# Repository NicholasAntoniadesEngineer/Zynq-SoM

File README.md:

# Zynq-SoM

A Zynq-7000 system-on-module + carrier board, with `schgen` — a netlist-first
KiCad schematic **and PCB** generator using C++ netlist definitions
to produce checked schematics and placed boards with component models and
multi-angle renders. Routing is deferred; these are not fabrication-ready boards.

The current published placement review is a **162×151 mm carrier** and
**98×98 mm devkit**. See the [release generation recipe and limitations](docs/RELEASE-2026-10-16.md)
to reproduce the committed images; the default commands below do not select
the carrier's qualified compact-placement recipe.

## Native build and test entry point

The C++ migration's Python-free build, dependency bootstrap and complete native
CTest entry point are documented in [`native/ci/README.md`](native/ci/README.md).
Use that path for native production builds. The transitional Python extension
and its build script are retired. Native `schgen check --tests-dir BUILD` runs
the full board, mutation/determinism selftest and complete CTest inventory.
All 393 inventoried tracked Python sources and tests are retired, along with
their dependency and lint configuration. Clean-tree acceptance is still in
progress; the commands below use the native executable.
All verification remains local, as required by the repository's no-CI policy.
No hosted workflow or gate bypass is introduced.

## The layers

1. **`parts/`** — one folder per physical part, named by MPN, GENERATED from
   LCSC/EasyEDA (`native/bin/schgen part-import --parts-root parts --lcsc C…`):
   pin table, symbol, footprint, 3D.
   See `parts/README.md`.
2. **`subsystems/`** — project-agnostic subsystem assets: interface contracts,
   READMEs, SPICE subcircuits and independent reference data. C++ netlist
   factories live in `native/src/authoring_*.cpp`; project adapters supply
   `bind`/`expects`/`buses`/`notes` metadata through the native registry.
   Scaffold a new one with `native/bin/schgen subsystem-new <name>`. See
   `subsystems/README.md`.
3. **`carrier/subsystems/`** — board subsystem assets and generated circuit
   projections. C++ project factories and adapters in `native/src/project_*.cpp`
   define the netlists; the J1/J2/J3 connector contract is extracted live from
   the SoM. Parts are resolved by library identity and named pins. See
   `carrier/README.md` and `carrier/subsystems/README.md`.
4. **The board** — `schgen` derives ALL geometry from netlist topology,
   proves it (netlist-equivalence + ERC + zero-overlap visual gates) and
   links the sheets into one KiCad project.

Plus `som/` — the hand-authored Zynq SoM KiCad project (open
`som/Zynq_SoM.kicad_pro`, KiCad 9+; its custom libs live in `som/lib/`).
The SoM↔carrier contract `carrier/som_interface.json` is extracted
programmatically (`schgen som-interface`), never hand-edited.

## Native regeneration

```bash
native/bin/schgen board --project carrier --timing
native/bin/schgen board --project devkit_mini --timing
# Diagnostic generation without output renders:
native/bin/schgen board --project carrier --no-render --timing
```

`--no-render` is diagnostic: it skips output renders, not mandatory electrical,
geometry or source-policy gates. Omit it for rendered acceptance. Use `--timing`
to measure this native implementation; historical Python timings do not apply.

`schgen build <name>` gates a single sheet (preview into a tempdir, nothing
committed). `schgen board` regenerates the committed outputs in place:
`carrier/Zynq_Carrier.kicad_pro` (open in KiCad), `schematic/`, `renders/`
(golden-snapshot drift detection), `reports/`,
`manufacturing/` (JLC BOM + layout constraints), and
`fpga/Zynq_Carrier_pins.xdc` — Vivado PACKAGE_PIN + IOSTANDARD for every
carrier port on a Zynq PL ball, ball map live-extracted from the SoM and
cross-checked against `som_interface.json` (also standalone: `schgen xdc`).

## The gate model

Every build fails unless every gate passes — the gates are judges, not knobs.
Schematic gates: **netlist** (KiCad's extracted netlist == the declared netlist,
pin for pin, so a junction that merges two nets is caught as a short), **ERC**
(zero errors), **visual** (zero overlap, zero wire crossings, junction-aware
short detection, fits the page). PCB gates: **DRC** (zero KiCad errors),
**3D-model** coverage + placement, **ratsnest** subsystem clustering, and
**connector** mating-face / spacing (off-board mouths, edge-flush). Architecture
+ gate definitions: `schgen/DESIGN.md`.

Local generation always runs its gates; native CTest is an additional check,
not a replacement. `schgen selftest` mutation-tests the gates themselves:
it injects one defect per class (pin swap, deleted wire, relabel, stray
no-connect, foreign-net junction short) and proves a gate kills each, then
builds twice and byte-compares for determinism.

```bash
native/bin/schgen selftest
```

## Process + where to read more

- The working rules and process contract (the immutable LAWs, the gate stack,
  the worktree/commit discipline) live in
  [`WORKING_GUIDELINES.txt`](docs/WORKING_GUIDELINES.txt).
- Layer guides: [`parts/README.md`](parts/README.md),
  [`subsystems/README.md`](subsystems/README.md) (the reusable library),
  [`carrier/README.md`](carrier/README.md),
  [`carrier/subsystems/README.md`](carrier/subsystems/README.md),
  and the engine contract [`schgen/DESIGN.md`](schgen/DESIGN.md).

<!-- schgen:gallery -->
<!-- GENERATED by `schgen gallery` — edits between these markers are overwritten -->
## Generated board + schematics

`schgen board` regenerates the placed-board 3D views, the block diagram and all 37 carrier sheets,
each PNG passing the netlist, ERC and visual gates.

<br>**[Ratsnest views](carrier/README.md#ratsnest-views)** — airwires per subsystem.

See **[carrier/README.md](carrier/README.md#generated-3d-board-views)** for all 8 board views + the full sheet gallery (thumbnails + descriptions).
<!-- /schgen:gallery -->

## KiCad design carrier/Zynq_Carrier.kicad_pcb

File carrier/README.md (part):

# carrier — the generated carrier board

Open `Zynq_Carrier.kicad_pro` with the KiCad version specified in
[`native/ci/README.md`](../native/ci/README.md). From the repository root,
regenerate the board outputs with `native/bin/schgen board --project carrier`
(the schematics, the placed
`Zynq_Carrier.kicad_pcb`, 3D renders, BOM, FPGA constraints, firmware contract,
and docs).

## Architecture (the locked decisions)

The carrier hosts a Zynq-7000 SoM over the J1/J2/J3 mezzanine:

- **Power input is USB-C PD only**, 20 V / 3 A via the FUSB302B, behind a
  TPS26631 eFuse with soft-start (controlled inrush + inlet OVP/OCP). No
  barrel jack.
- **The SoM is a 4.2–5 V module — it must NEVER see the 20 V rail** (P0, the
  most important electrical decision). An **always-on `+5V_SOM` buck**
  (its own `power_som` sheet) feeds the SoM's J1 VIN pins; always-on because
  PD negotiation is circular (the system controller must boot first).
- **Carrier bucks win over the SoM's exported rails** — the SoM's +3V3/+1V8
  on J1 are isolated (NC / TP-only); carrier rails are +5V, +3V3, +1V8, plus
  per-module **gated rails** (+5V_USB, +3V3_SD, the HDMI/LCD/CAM/PMOD/AUX
  rails) sourced by bring-up load switches.
- **Bring-up is staged with switches**: a DIP switch AND a system-controller
  GPIO override drive every regulator/module enable; per-rail power-good LEDs;
  rails come up one at a time. New board-services HW (ID-EEPROM, RTC, QWIIC,
  watchdog) sits behind the same gated `+3V3_AUX` rail and a PCA9306 I2C
  isolator (so the gated bus can never back-power the always-on management I2C).
- **microSD carries a mandatory 1.8 V ↔ 3.3 V level translator** (TXS02612):
  the SoM exposes SDIO at 1.8 V, but SD cards init at 3.3 V.
- **Stackup is JLCPCB 4-layer JLC04161H-7628**; its impedance geometry drives
  the exported layout constraints (90 Ω USB, 100 Ω TMDS/LVDS/MIPI). The user
  owns the PCB outline + placement — the floorplan kit is a suggestion.

## The subsystem / adapter pattern

A board sheet is one Python netlist under `subsystems/` — **the only
hand-written layer**. There are two flavours:

- **Thin adapters over the reusable library.** A portable subsystem lives in
  the project-agnostic top-level [`subsystems/`](../subsystems/README.md)
  library with ABSTRACT port/rail names; the carrier consumes it with a tiny
  adapter that declares ONE module-level `META` dict and forwards it —
  `return _lib.circuit(META)`. `META["bind"]` renames the abstract nets to the
  carrier's real net names (order-preserving, so the emitted sheet is
  byte-identical to a hand-written one); `expects` / `buses` / `notes` carry
  the project-specific linker deferrals, bus names and house-style prose. The
  contract is `schgen/core/subsystem.py` (`Meta`); a typo'd top-level key is a
  hard `CircuitError`. 17 subsystems use the reusable library this way (usb_pd, usbc_otg,
  uart_bridge, usb_jtag, ethernet, hdmi_tx, hdmi_rx, lcd, microsd, camera, pmod,
  pmod_expansion, pd_input, power, rj45_connector, usb_uart_connector,
  usb_jtag_connector) — see [`subsystems/README.md`](../subsystems/README.md).
- **Carrier-specific glue stays local.** Sheets that only make sense for this
  board — the J1/J2/J3 connector sheets, the bring-up + power + power-monitor
  sheets, the board-services HW, the carrier connectors — are authored directly
  under `subsystems/` as full netlists. See
  [`subsystems/README.md`](subsystems/README.md) for the authoring guide.

Either way the rule is the same: **the .py is the NETLIST, never geometry.**
No coordinates, no wire plans, no text positions; a purity gate AST-scans every
subsystem and fails the build if it defines `placer` or imports a geometry API.
All placement is derived from circuit topology by `schgen/layout/place.py`.

- `subsystems/` — the authored netlists (adapters + local glue), the only
  hand-written layer; see `subsystems/README.md`.
- `Zynq_Carrier.kicad_sch` + `schematic/` — the root sheet + sub-sheets
  (hierarchy mode, board-unique references), committed.
- `renders/` — one PNG per sheet, committed and reviewable on GitHub;
  `golden.json` holds perceptual hashes — drift warns, `schgen board
  --bless` accepts intentional changes.
- `reports/` — per-sheet ERC, gate verdicts, link report, board netlist
  gate: the proof travels with the design.
- `manufacturing/` — `bom_jlc.csv` + JLC04161H-7628 layout constraints.
- `fpga/` — `Zynq_Carrier_pins.xdc`, GENERATED Vivado pin constraints
  (`schgen xdc`): every carrier port on a Zynq PL ball through J2/J3,
  ball map live-extracted from the SoM project (never hand-typed),
  cross-checked against `som_interface.json` (stale contract = build
  FAIL), IOSTANDARD from the PLAN VCCO rail map.
- `som_interface.json` — the SoM↔carrier J1/J2/J3 contract, extracted
  programmatically (`schgen som-interface`), never hand-edited.
- `nets.py` — the GENERATED cross-sheet net-name contract
  (`schgen nets`).
- `research/` — the per-subsystem engineering dossiers (datasheet-grounded,
  hand-written): [`bringup_power_gating.md`](research/bringup_power_gating.md),
  [`camera_csi.md`](research/camera_csi.md),
  [`debug_boot_pmod.md`](research/debug_boot_pmod.md), [`fmc.md`](research/fmc.md),
  [`lcd_backlight.md`](research/lcd_backlight.md), [`power_mon.md`](research/power_mon.md),
  [`thermal_bucks.md`](research/thermal_bucks.md),
  [`usb_jtag_pmod_expansion.md`](research/usb_jtag_pmod_expansion.md),
  [`user_io.md`](research/user_io.md), [`wave3_function_map.md`](research/wave3_function_map.md).
- `docs/` — the design-documentation packet:
  [`DESIGN_SPEC.md`](docs/DESIGN_SPEC.md) (theory of operation: mezzanine
  interface, power architecture + sequencing, every subsystem),
  [`COMPLIANCE.md`](docs/COMPLIANCE.md) (per-interface checklists: HDMI,
  Gigabit Ethernet, USB 2.0, MIPI CSI-2, USB-PD, SoM bank-35 IO header),
  [`BRINGUP.md`](docs/BRINGUP.md), [`TEST_PLAN.md`](docs/TEST_PLAN.md),
  [`FLOORPLAN.md`](docs/FLOORPLAN.md), and the generated diagrams
  `block_diagram.svg` / `power_tree.svg` / `power_sequence.svg`.

## Assembly + bring-up procedure

Human steps the netlist cannot carry. Everything else — every component value
and every bind decision — is a registered basis entry in `carrier/basis.py`
(`REGISTRY` for values, `BINDS` for net binds), not prose.

**Before fab**

- **QWIIC pad order (`board_qwiic` J1).** Pads 1–4 are the QWIIC standard
  GND / +3V3 / SDA / SCL looking into the receptacle; pads 5/6 are the shell
  tabs. Confirm pad 1's location against the J1 footprint silk before release —
  a swapped power pad damages every external module plugged in.
- **Chassis star stitch (`mechanical`).** `GND` ↔ `CHASSIS_GND` must be joined
  at exactly one point in copper. See
  [`subsystems/mechanical/README.md`](subsystems/mechanical/README.md).

**Stuffing**

- **RTC backup cell (`board_services` BT1).** Fit a **rechargeable ML1220**
  (Mn-Li). The SC firmware enables the RV-3028 trickle charger, so the cell
  tops up whenever the board is powered. Do **NOT** fit a primary CR1220 (it
  would be charged) and do **NOT** fit a LIR Li-ion (its 4.2 V charge target
  exceeds the 3.3 V supply). The KH-CR1220-2 holder accepts both 12.5 mm
  chemistries, so the holder will not stop the wrong cell.
- **HDMI-RX termination (`hdmi_rx_term`).** The 8 × 49.9 Ω sink terminations
  belong physically next to Zynq bank 33, not at the connector. An optional
  0 Ω / ferrite may be fitted in the +3V3 → AVCC trace to island the supply.
- **Camera terminations (`camera` R1–R3).** Place the 100 Ω differential
  terminations at the **SoM-connector** end of the traces, not at the FFC.

**Powering up**

- Every rail and module enable is a DIP switch ANDed with a system-controller
  override, so a blank SC still boots "switches only". Bring rails up one at a
  time and read the per-rail power-good LED.
- `+5V_SOM`, `+3V3_SC` and the debug island (`+5V_DBG` / `+3V3_DBG`, alive only
  with the debug USB-C cable plugged) are **always-on by design** — they are not
  gated and will be live before you touch a switch.
- Probe every EN line and every gated rail at its own test point; the gated
  rails are probed at the SY6280 output, on the source side of the module
  connector.
- ESC leads on the `motor_pwm` header use SIG + GND only — keep the ESC's own
  BEC off the +5 V row.

## Build + gate discipline

There is **no CI** — instead every local `schgen build <sheet>` /
`schgen board` runs the full gate stack and exits non-zero on any failure, so
nothing un-gated ever gets committed. The committed `reports/` are the proof.
The gates (never edited to pass — LAW 4; strengthening one is the work,
loosening it is forbidden):

- **PURITY** — the subsystem source is netlist-only (no `placer`, no geometry
  import); AST-scanned before execution.
- **MODEL COMPLETENESS** — every pin is netted or explicitly `c.nc()`'d; every
  input is driven.
- **NETLIST** — KiCad's own extracted netlist == the declared netlist, pin for
  pin (the unfakeable electrical proof — catches shorts, opens, single-pin
  nets, NC-cheats, name drift).
- **ERC** — kicad-cli ERC, zero errors.
- **VISUAL** — zero overlap, zero crossings, fits the page (no exemptions).
- **CC short/open** — an independent net-blind union-find over the emitted
  geometry, a 2nd oracle that agrees with the netlist gate pin-for-pin.
- **BOARD GATE + LINK** — every linked net merges correctly across sheets;
  typed-port contract resolved (diff pairs, I2C, sd_bus levels, `expect=`
  deferrals).
- **POWER-TREE / TEST-POINT / THERMAL / DESIGN-RULE / SPICE** — per-regulator
  headroom, a probe per rail/bus, per-device Tj, decoupling/pull-up/strap
  completeness, and divider/feedback/ramp setpoints.
- **PCB** — the placed `Zynq_Carrier.kicad_pcb` passes DRC (zero KiCad errors),
  3D-model coverage + placement, ratsnest subsystem clustering, connector
  mating-face (off-board mouths) + spacing, and refdes-overlap; multi-angle 3D
  board renders are written for visual review.

`schgen selftest` mutation-tests the gates themselves (it injects one defect
per class — pin swap, deleted wire, relabel, stray NC, foreign-net junction
short — and proves a gate kills each) and builds twice for byte-determinism
(across PYTHONHASHSEED). Reusable subsystem packages also carry an offline
local `test_<name>.py`; cross-board gates stay aggregated at board level.

The working rhythm: build → read the gate verdicts → **open the render PNGs and
inspect them like a PCB reviewer** (the render is the deliverable) → commit per
verified unit. Heavy/parallel work runs in isolated git worktrees harvested
sequentially; deterministic output means a regen on the merged state produces
zero artifact diff. The full process contract is
[`../WORKING_GUIDELINES.txt`](../docs/WORKING_GUIDELINES.txt).

<!-- schgen:gallery -->
<!-- GENERATED by `schgen gallery` — edits between these markers are overwritten -->
## Generated 3D board views

The placed board rendered from 8 angles by `schgen board` (kicad-cli, the real component 3D models) — regenerated and committed every build, just like the sheets below.

|   |   |   |   |
|---|---|---|---|
| <br>**Perspective (front)** | <br>**Perspective (rear)** | <br>**Top** | <br>**Bottom** |
| <br>**Front edge** | <br>**Back edge** | <br>**Left edge** | <br>**Right edge** |

## Ratsnest views

Placed-board airwires, regenerated by `schgen board`: blue/orange = the subsystem's parts (top/bottom side), steel = SoM, green = intra-subsystem, red = to the SoM. `wired` = in `placement.wired_sheets`.

|   |   |
|---|---|
| <br>**Board (top)** | <br>**Board (bottom)** |
| <br>**SoM region** |   |

|   |   |   |   |
|---|---|---|---|
| <br>**board_aux** | <br>**board_qwiic** `wired` | <br>**board_services** | <br>**bringup_en** |
| <br>**bringup_en_modules** | <br>**bringup_modules** | <br>**bringup_rails** | <br>**camera** `wired` |
| <br>**debug_boot** | <br>**ethernet** `wired` | <br>**fmc** `wired` | <br>**hdmi_rx** `wired` |
| <br>**hdmi_rx_term** `wired` | <br>**hdmi_tx** `wired` | <br>**lcd** `wired` | <br>**mechanical** |
| <br>**microsd** `wired` | <br>**motor_pwm** `wired` | <br>**motor_sense** `wired` | <br>**pd_input** `wired` |
| <br>**pmod** `wired` | <br>**pmod_expansion** `wired` | <br>**power** `wired` | <br>**power_mon** `wired` |
| <br>**power_som** `wired` | <br>**rj45_connector** | <br>**uart_bridge** `wired` | <br>**usb_jtag** `wired` |
| <br>**usb_jtag_connector** `wired` | <br>**usb_pd** `wired` | <br>**usb_uart_connector** `wired` | <br>**usbc_otg** `wired` |
| <br>**user_io** |   |   |   |

## Generated schematics

Block diagram and all 37 carrier sheets, regenerated by `schgen board` —
every PNG below passed the netlist, ERC and visual gates.

|   |   |   |
|---|---|---|
| <br>**board_aux** | <br>**board_qwiic** | <br>**board_services** |
| <br>**bringup_en** | <br>**bringup_en_modules** | <br>**bringup_modules** |
| <br>**bringup_rails** | <br>**camera** | <br>**debug_boot** |
| <br>**ethernet** | <br>**fmc** | <br>**hdmi_rx** |
| <br>**hdmi_rx_term** | <br>**hdmi_tx** | <br>**lcd** |
| <br>**mechanical** | <br>**microsd** | <br>**motor_pwm** |
| <br>**motor_sense** | <br>**pd_input** | <br>**pmod** |
| <br>**pmod_expansion** | <br>**power** | <br>**power_mon** |
| <br>**power_som** | <br>**rj45_connector** | <br>**som_decoupling** |
| <br>**som_j1** | <br>**som_j2** | <br>**som_j3** |
| <br>**uart_bridge** | <br>**usb_jtag** | <br>**usb_jtag_connector** |
| <br>**usb_pd** | <br>**usb_uart_connector** | <br>**usbc_otg** |
| <br>**user_io** |   |   |

| sheet | description |
|---|---|
| [board_aux](renders/board_aux.png) | Board services: gated +3V3_AUX rail + PCA9306 I2C isolator |
| [board_qwiic](renders/board_qwiic.png) | QWIIC / STEMMA-QT expansion connector + USBLC6 ESD array |
| [board_services](renders/board_services.png) | Board services: ID-EEPROM, RTC, watchdog, QWIIC |
| [bringup_en](renders/bringup_en.png) | Bring-up EN cells: 3x SN74LVC1G08 rail DIP-AND-override |
| [bringup_en_modules](renders/bringup_en_modules.png) | Bring-up EN cells: 11x SN74LVC1G08 module DIP-AND-override |
| [bringup_modules](renders/bringup_modules.png) | Bring-up module gates: 10x SY6280 + status/user LEDs |
| [bringup_rails](renders/bringup_rails.png) | Bring-up controls: rail/module DIPs + TCA9535 + buttons |
| [camera](renders/camera.png) | RPi camera port: 2-lane MIPI CSI-2 (15P FFC) |
| [debug_boot](renders/debug_boot.png) | JTAG + SWD headers, boot-request DIP, reset |
| [ethernet](renders/ethernet.png) | Ethernet: HX5008NL magnetics + Bob-Smith |
| [fmc](renders/fmc.png) | SoM bank-35 IO breakout (2x20 2.54mm header, VADJ 2.5V) |
| [hdmi_rx](renders/hdmi_rx.png) | HDMI RX: HDMI-A sink + EDID EEPROM |
| [hdmi_rx_term](renders/hdmi_rx_term.png) | HDMI-RX TMDS sink termination (8x49.9R to AVCC=+3V3) |
| [hdmi_tx](renders/hdmi_tx.png) | HDMI TX: TPD12S016 + HDMI-A receptacle (source) |
| [lcd](renders/lcd.png) | 40-pin TTL RGB LCD + SY7201 backlight boost |
| [mechanical](renders/mechanical.png) | Mechanical: M3 mounts + chassis-GND bond (fiducials are PCB-only, emitted by the placer) |
| [microsd](renders/microsd.png) | microSD slot (1.8V SoM <-> 3.3V card, TXS02612) |
| [motor_pwm](renders/motor_pwm.png) | 8-ch PWM/ESC output buffer (5V, PL-isolating) |
| [motor_sense](renders/motor_sense.png) | ESC motor-rail telemetry: INA3221 + 10mR shunt (I2C 0x42) |
| [pd_input](renders/pd_input.png) | Power inlet: USB-C PD 20V/3A + TPS26631 eFuse |
| [pmod](renders/pmod.png) | 2x Pmod host ports (bank 13, 200R series, gated 3V3) |
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
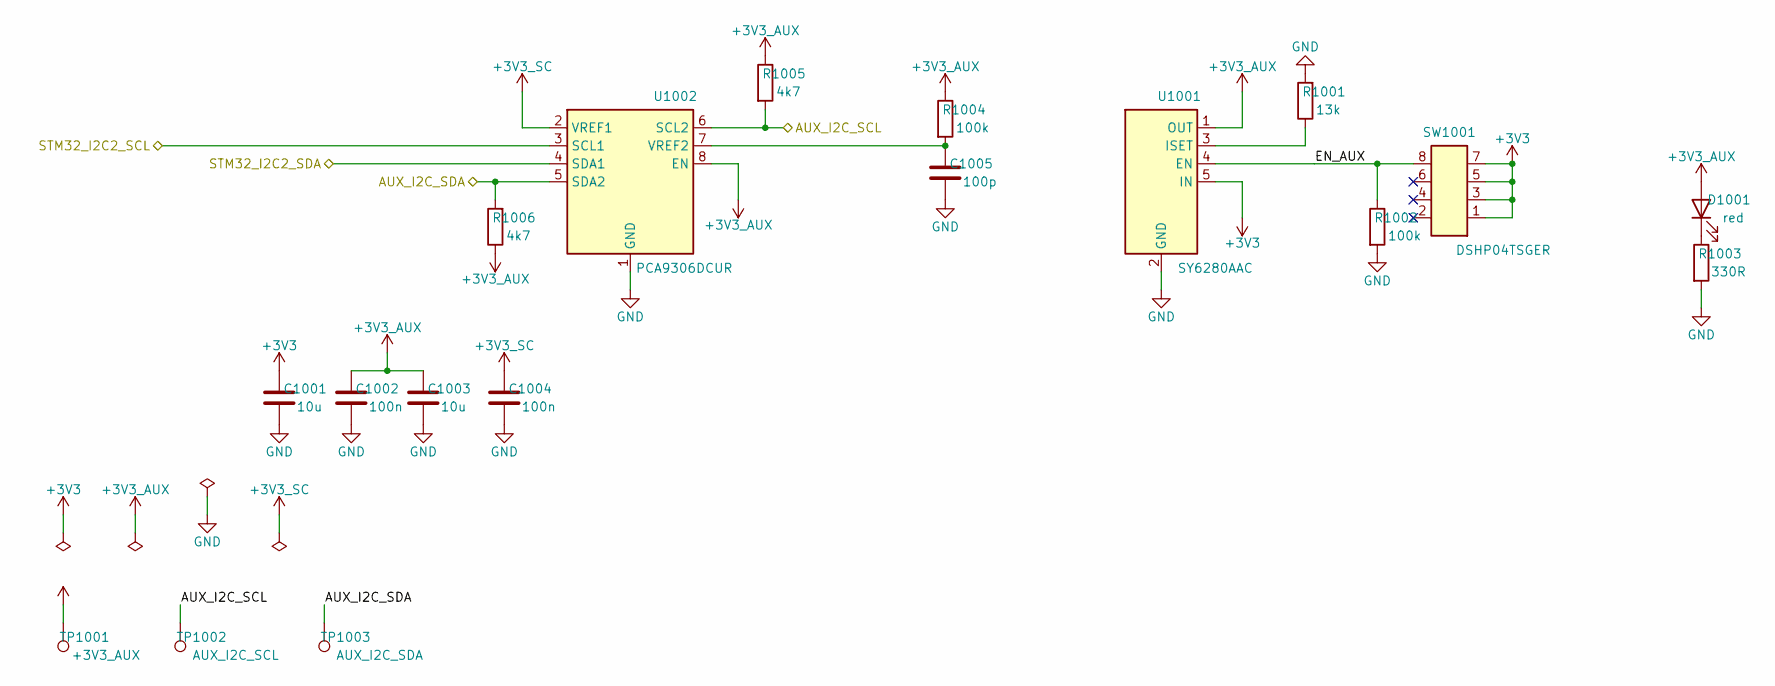
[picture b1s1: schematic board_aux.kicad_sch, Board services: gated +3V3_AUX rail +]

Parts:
C1001, C1003: 10u; C_0805_2012Metric; LCSC C15850
C1002, C1004: 100n; C_0603_1608Metric; LCSC C14663
C1005: 100p; C_0603_1608Metric; LCSC C14858
D1001: red; LED_0603_1608Metric; LCSC C2286
R1001: 13k; R_0603_1608Metric; LCSC C22797
R1002, R1004: 100k; R_0603_1608Metric; LCSC C25803
R1003: 330R; R_0603_1608Metric; LCSC C23138
R1005, R1006: 4k7; R_0603_1608Metric; LCSC C23162
SW1001: DSHP04TSGER; LCSC C3293144
TP1001: +3V3_AUX; TestPoint_Pad_D1.5mm
TP1002: AUX_I2C_SCL; TestPoint_Pad_D1.5mm
TP1003: AUX_I2C_SDA; TestPoint_Pad_D1.5mm
U1001: SY6280AAC; LCSC C55136
U1002: PCA9306DCUR; LCSC C33196

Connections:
+3V3: C1001.1, SW1001.1, SW1001.3, SW1001.5, SW1001.7, U1001.5 (IN); also elsewhere on the board
+3V3_AUX: C1002.1, C1003.1, D1001.2 (A), R1004.1, R1005.1, R1006.1, TP1001.1, U1001.1 (OUT), U1002.8 (EN); also elsewhere on the board
+3V3_SC: C1004.1, U1002.2 (VREF1); also elsewhere on the board
/board_aux/EN_AUX: R1002.1, SW1001.8, U1001.4 (EN)
AUX_I2C_SCL: R1005.2, TP1002.1, U1002.6 (SCL2); also elsewhere on the board
AUX_I2C_SDA: R1006.2, TP1003.1, U1002.5 (SDA2); also elsewhere on the board
GND: C1001.2, C1002.2, C1003.2, C1004.2, C1005.2, R1001.2, R1002.2, R1003.2, U1001.2 (GND), U1002.1 (GND); also elsewhere on the board
unnamed: D1001.1 (K), R1003.1
unnamed: R1001.1, U1001.3 (ISET)
unnamed: C1005.1, R1004.2, U1002.7 (VREF2)
STM32_I2C2_SCL: U1002.3 (SCL1); also elsewhere on the board
STM32_I2C2_SDA: U1002.4 (SDA1); also elsewhere on the board

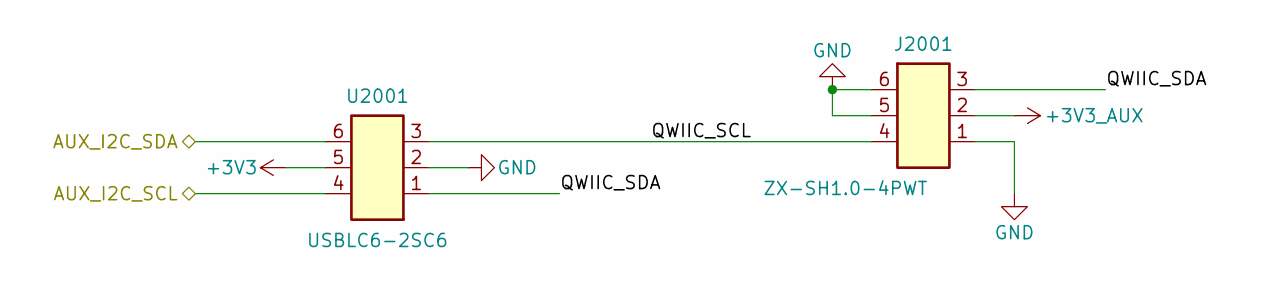
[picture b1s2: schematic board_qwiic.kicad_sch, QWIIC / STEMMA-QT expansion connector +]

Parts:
J2001: ZX-SH1.0-4PWT; LCSC C7430446
U2001: USBLC6-2SC6; LCSC C7519

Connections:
+3V3: U2001.5; also elsewhere on the board
+3V3_AUX: J2001.2; also elsewhere on the board
/board_qwiic/QWIIC_SCL: J2001.4, U2001.3
/board_qwiic/QWIIC_SDA: J2001.3, U2001.1
AUX_I2C_SCL: U2001.4; also elsewhere on the board
AUX_I2C_SDA: U2001.6; also elsewhere on the board
GND: J2001.1, J2001.5, J2001.6, U2001.2; also elsewhere on the board

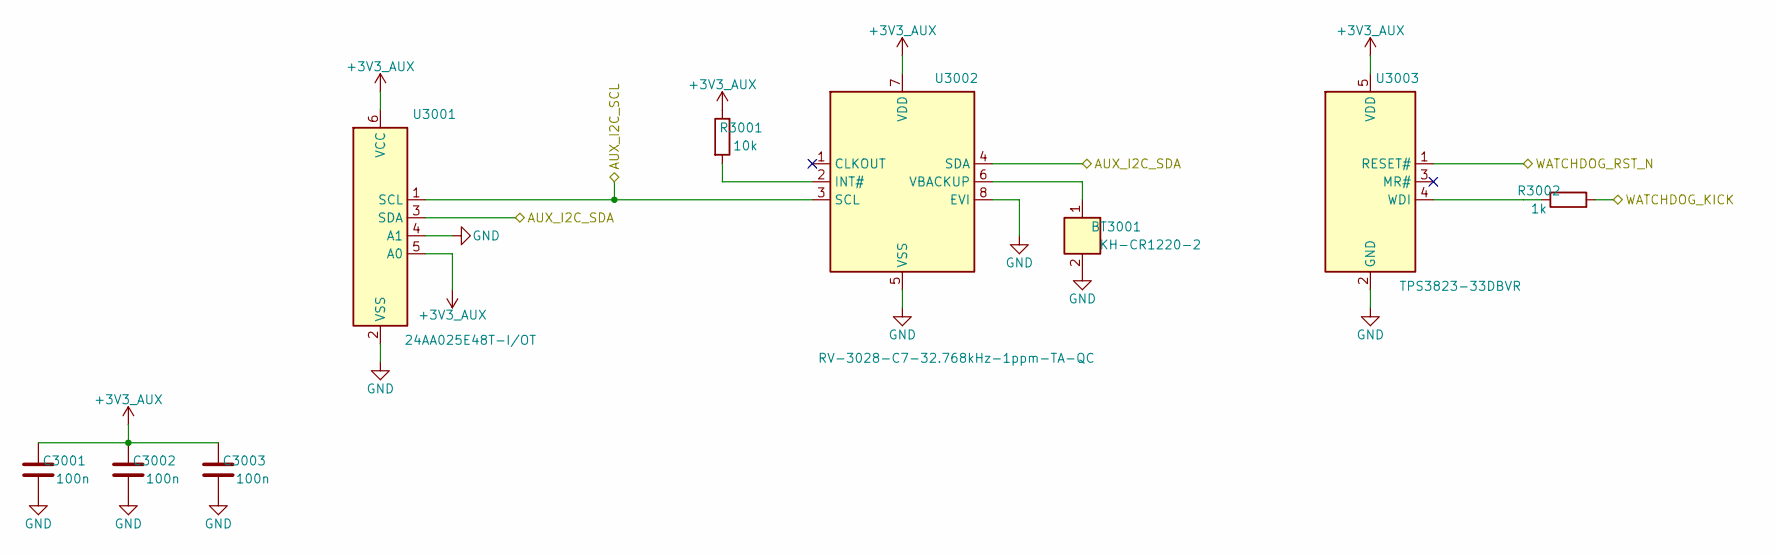
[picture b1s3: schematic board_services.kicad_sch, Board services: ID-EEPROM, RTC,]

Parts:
BT3001: KH-CR1220-2; LCSC C5365933
C3001, C3002, C3003: 100n; C_0603_1608Metric; LCSC C14663
R3001: 10k; R_0603_1608Metric; LCSC C25804
R3002: 1k; R_0603_1608Metric; LCSC C21190
U3001: 24AA025E48T-I/OT; 24AA025E48T-I_OT; LCSC C129895
U3002: RV-3028-C7-32.768kHz-1ppm-TA-QC; LCSC C3019759
U3003: TPS3823-33DBVR; LCSC C7719

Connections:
+3V3_AUX: C3001.1, C3002.1, C3003.1, R3001.1, U3001.5 (A0), U3001.6 (VCC), U3002.7 (VDD), U3003.5 (VDD); also elsewhere on the board
AUX_I2C_SCL: U3001.1 (SCL), U3002.3 (SCL); also elsewhere on the board
AUX_I2C_SDA: U3001.3 (SDA), U3002.4 (SDA); also elsewhere on the board
GND: BT3001.2, C3001.2, C3002.2, C3003.2, U3001.2 (VSS), U3001.4 (A1), U3002.5 (VSS), U3002.8 (EVI), U3003.2 (GND); also elsewhere on the board
unnamed: R3001.2, U3002.2 (INT#)
unnamed: BT3001.1, U3002.6 (VBACKUP)
unnamed: R3002.2, U3003.4 (WDI)
WATCHDOG_KICK: R3002.1; also elsewhere on the board
WATCHDOG_RST_N: U3003.1 (RESET#); also elsewhere on the board

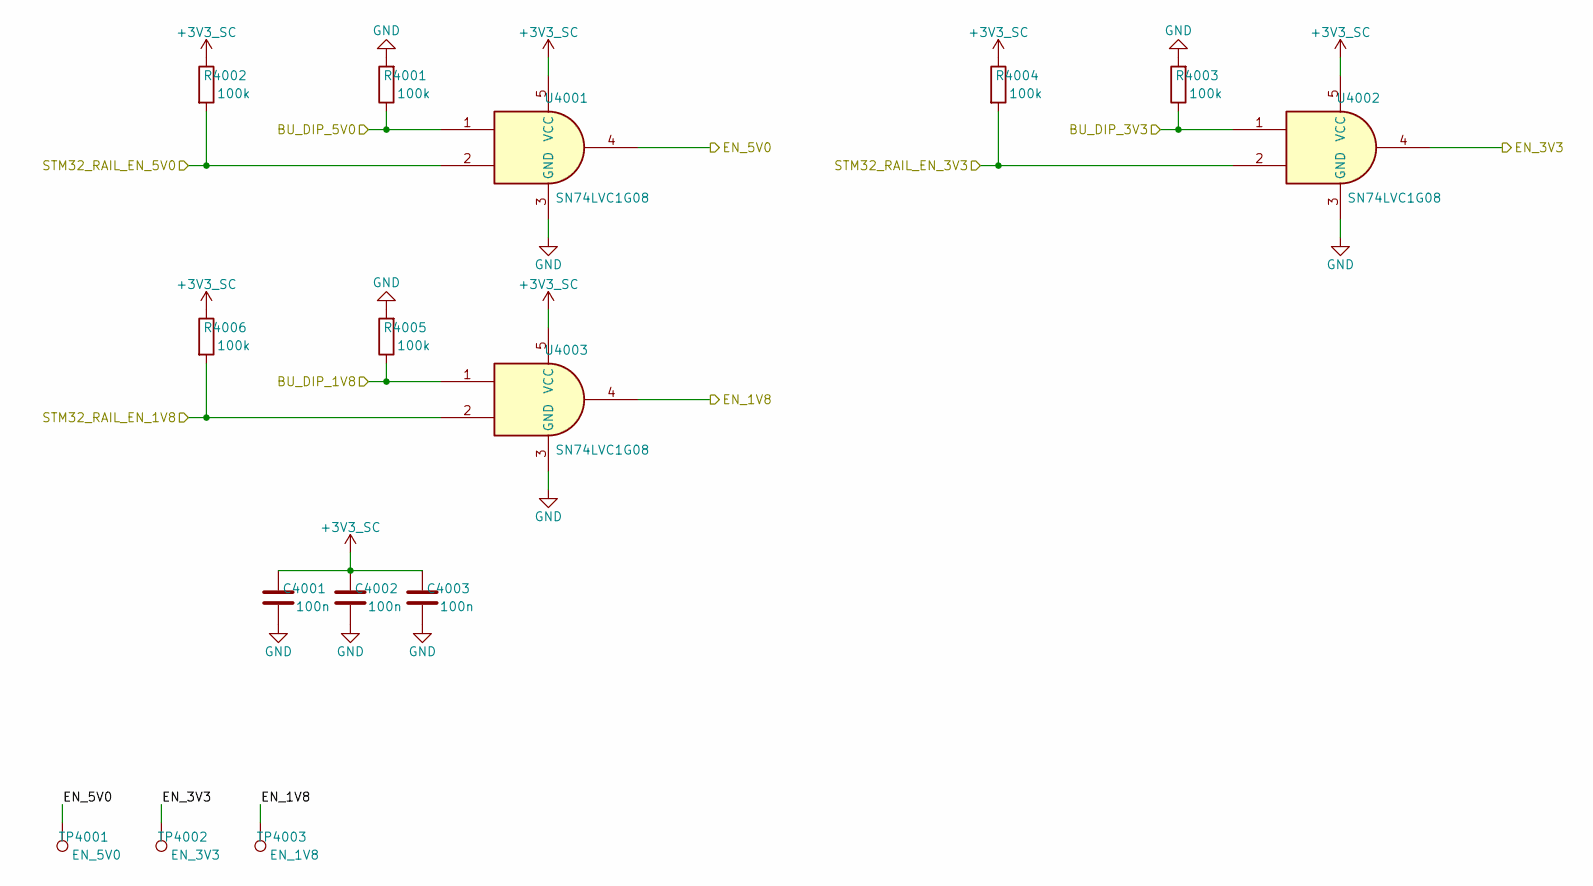
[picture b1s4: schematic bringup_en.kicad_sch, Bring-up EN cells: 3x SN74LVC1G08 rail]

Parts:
C4001, C4002, C4003: 100n; C_0603_1608Metric; LCSC C14663
R4001, R4002, R4003, R4004, R4005, R4006: 100k; R_0603_1608Metric; LCSC C25803
TP4001: EN_5V0; TestPoint_Pad_D1.5mm
TP4002: EN_3V3; TestPoint_Pad_D1.5mm
TP4003: EN_1V8; TestPoint_Pad_D1.5mm
U4001, U4002, U4003: SN74LVC1G08; SOT-23-5; LCSC C7666

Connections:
+3V3_SC: C4001.1, C4002.1, C4003.1, R4002.1, R4004.1, R4006.1, U4001.5 (VCC), U4002.5 (VCC), U4003.5 (VCC); also elsewhere on the board
BU_DIP_1V8: R4005.1, U4003.1; also elsewhere on the board
BU_DIP_3V3: R4003.1, U4002.1; also elsewhere on the board
BU_DIP_5V0: R4001.1, U4001.1; also elsewhere on the board
EN_1V8: TP4003.1, U4003.4; also elsewhere on the board
EN_3V3: TP4002.1, U4002.4; also elsewhere on the board
EN_5V0: TP4001.1, U4001.4; also elsewhere on the board
GND: C4001.2, C4002.2, C4003.2, R4001.2, R4003.2, R4005.2, U4001.3 (GND), U4002.3 (GND), U4003.3 (GND); also elsewhere on the board
STM32_RAIL_EN_1V8: R4006.2, U4003.2; also elsewhere on the board
STM32_RAIL_EN_3V3: R4004.2, U4002.2; also elsewhere on the board
STM32_RAIL_EN_5V0: R4002.2, U4001.2; also elsewhere on the board

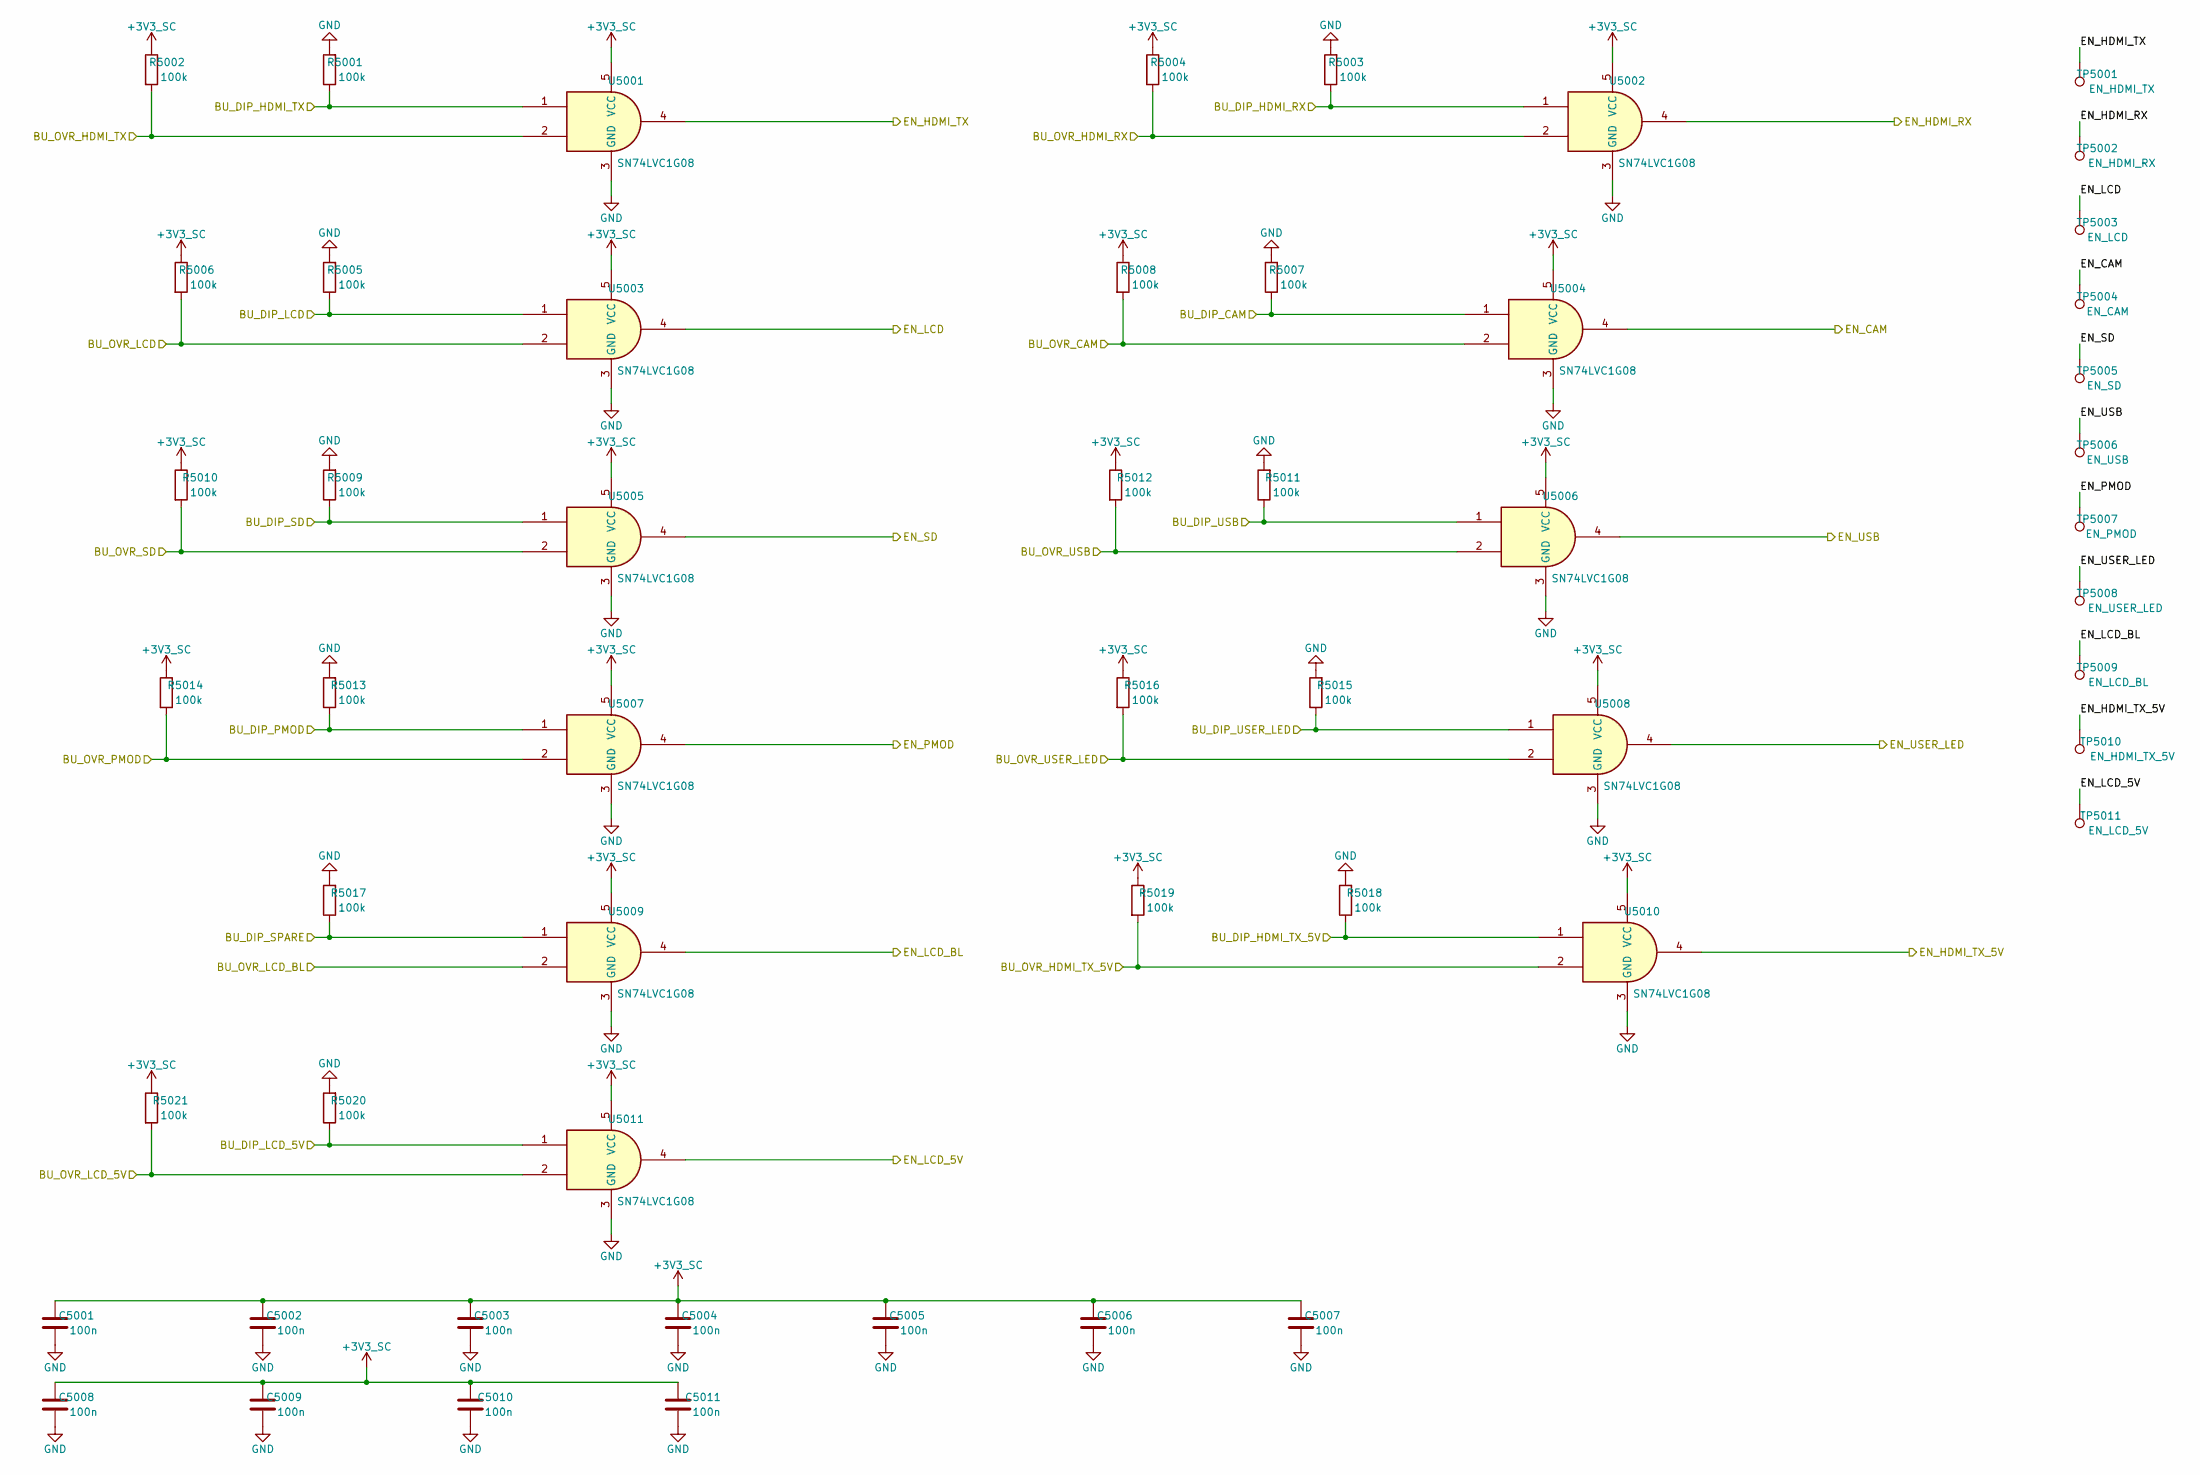
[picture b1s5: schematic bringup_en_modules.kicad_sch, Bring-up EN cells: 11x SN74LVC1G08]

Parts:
C5001, C5002, C5003, C5004, C5005, C5006, C5007, C5008, C5009, C5010, C5011: 100n; C_0603_1608Metric; LCSC C14663
R5001, R5002, R5003, R5004, R5005, R5006, R5007, R5008, R5009, R5010, R5011, R5012, R5013, R5014, R5015, R5016, R5017, R5018, R5019, R5020, R5021: 100k; R_0603_1608Metric; LCSC C25803
TP5001: EN_HDMI_TX; TestPoint_Pad_D1.5mm
TP5002: EN_HDMI_RX; TestPoint_Pad_D1.5mm
TP5003: EN_LCD; TestPoint_Pad_D1.5mm
TP5004: EN_CAM; TestPoint_Pad_D1.5mm
TP5005: EN_SD; TestPoint_Pad_D1.5mm
TP5006: EN_USB; TestPoint_Pad_D1.5mm
TP5007: EN_PMOD; TestPoint_Pad_D1.5mm
TP5008: EN_USER_LED; TestPoint_Pad_D1.5mm
TP5009: EN_LCD_BL; TestPoint_Pad_D1.5mm
TP5010: EN_HDMI_TX_5V; TestPoint_Pad_D1.5mm
TP5011: EN_LCD_5V; TestPoint_Pad_D1.5mm
U5001, U5002, U5003, U5004, U5005, U5006, U5007, U5008, U5009, U5010, U5011: SN74LVC1G08; SOT-23-5; LCSC C7666

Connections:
+3V3_SC: C5001.1, C5002.1, C5003.1, C5004.1, C5005.1, C5006.1, C5007.1, C5008.1, C5009.1, C5010.1, C5011.1, R5002.1, R5004.1, R5006.1, R5008.1, R5010.1, R5012.1, R5014.1, R5016.1, R5019.1, R5021.1, U5001.5 (VCC), U5002.5 (VCC), U5003.5 (VCC), U5004.5 (VCC), U5005.5 (VCC), U5006.5 (VCC), U5007.5 (VCC), U5008.5 (VCC), U5009.5 (VCC), U5010.5 (VCC), U5011.5 (VCC); also elsewhere on the board
BU_DIP_CAM: R5007.1, U5004.1; also elsewhere on the board
BU_DIP_HDMI_RX: R5003.1, U5002.1; also elsewhere on the board
BU_DIP_HDMI_TX: R5001.1, U5001.1; also elsewhere on the board
BU_DIP_HDMI_TX_5V: R5018.1, U5010.1; also elsewhere on the board
BU_DIP_LCD: R5005.1, U5003.1; also elsewhere on the board
BU_DIP_LCD_5V: R5020.1, U5011.1; also elsewhere on the board
BU_DIP_PMOD: R5013.1, U5007.1; also elsewhere on the board
BU_DIP_SD: R5009.1, U5005.1; also elsewhere on the board
BU_DIP_SPARE: R5017.1, U5009.1; also elsewhere on the board
BU_DIP_USB: R5011.1, U5006.1; also elsewhere on the board
BU_DIP_USER_LED: R5015.1, U5008.1; also elsewhere on the board
BU_OVR_CAM: R5008.2, U5004.2; also elsewhere on the board
BU_OVR_HDMI_RX: R5004.2, U5002.2; also elsewhere on the board
BU_OVR_HDMI_TX: R5002.2, U5001.2; also elsewhere on the board
BU_OVR_HDMI_TX_5V: R5019.2, U5010.2; also elsewhere on the board
BU_OVR_LCD: R5006.2, U5003.2; also elsewhere on the board
BU_OVR_LCD_5V: R5021.2, U5011.2; also elsewhere on the board
BU_OVR_LCD_BL: U5009.2; also elsewhere on the board
BU_OVR_PMOD: R5014.2, U5007.2; also elsewhere on the board
BU_OVR_SD: R5010.2, U5005.2; also elsewhere on the board
BU_OVR_USB: R5012.2, U5006.2; also elsewhere on the board
BU_OVR_USER_LED: R5016.2, U5008.2; also elsewhere on the board
EN_CAM: TP5004.1, U5004.4; also elsewhere on the board
EN_HDMI_RX: TP5002.1, U5002.4; also elsewhere on the board
EN_HDMI_TX: TP5001.1, U5001.4; also elsewhere on the board
EN_HDMI_TX_5V: TP5010.1, U5010.4; also elsewhere on the board
EN_LCD: TP5003.1, U5003.4; also elsewhere on the board
EN_LCD_5V: TP5011.1, U5011.4; also elsewhere on the board
EN_LCD_BL: TP5009.1, U5009.4
EN_PMOD: TP5007.1, U5007.4; also elsewhere on the board
EN_SD: TP5005.1, U5005.4; also elsewhere on the board
EN_USB: TP5006.1, U5006.4; also elsewhere on the board
EN_USER_LED: TP5008.1, U5008.4; also elsewhere on the board
GND: C5001.2, C5002.2, C5003.2, C5004.2, C5005.2, C5006.2, C5007.2, C5008.2, C5009.2, C5010.2, C5011.2, R5001.2, R5003.2, R5005.2, R5007.2, R5009.2, R5011.2, R5013.2, R5015.2, R5017.2, R5018.2, R5020.2, U5001.3 (GND), U5002.3 (GND), U5003.3 (GND), U5004.3 (GND), U5005.3 (GND), U5006.3 (GND), U5007.3 (GND), U5008.3 (GND), U5009.3 (GND), U5010.3 (GND), U5011.3 (GND); also elsewhere on the board

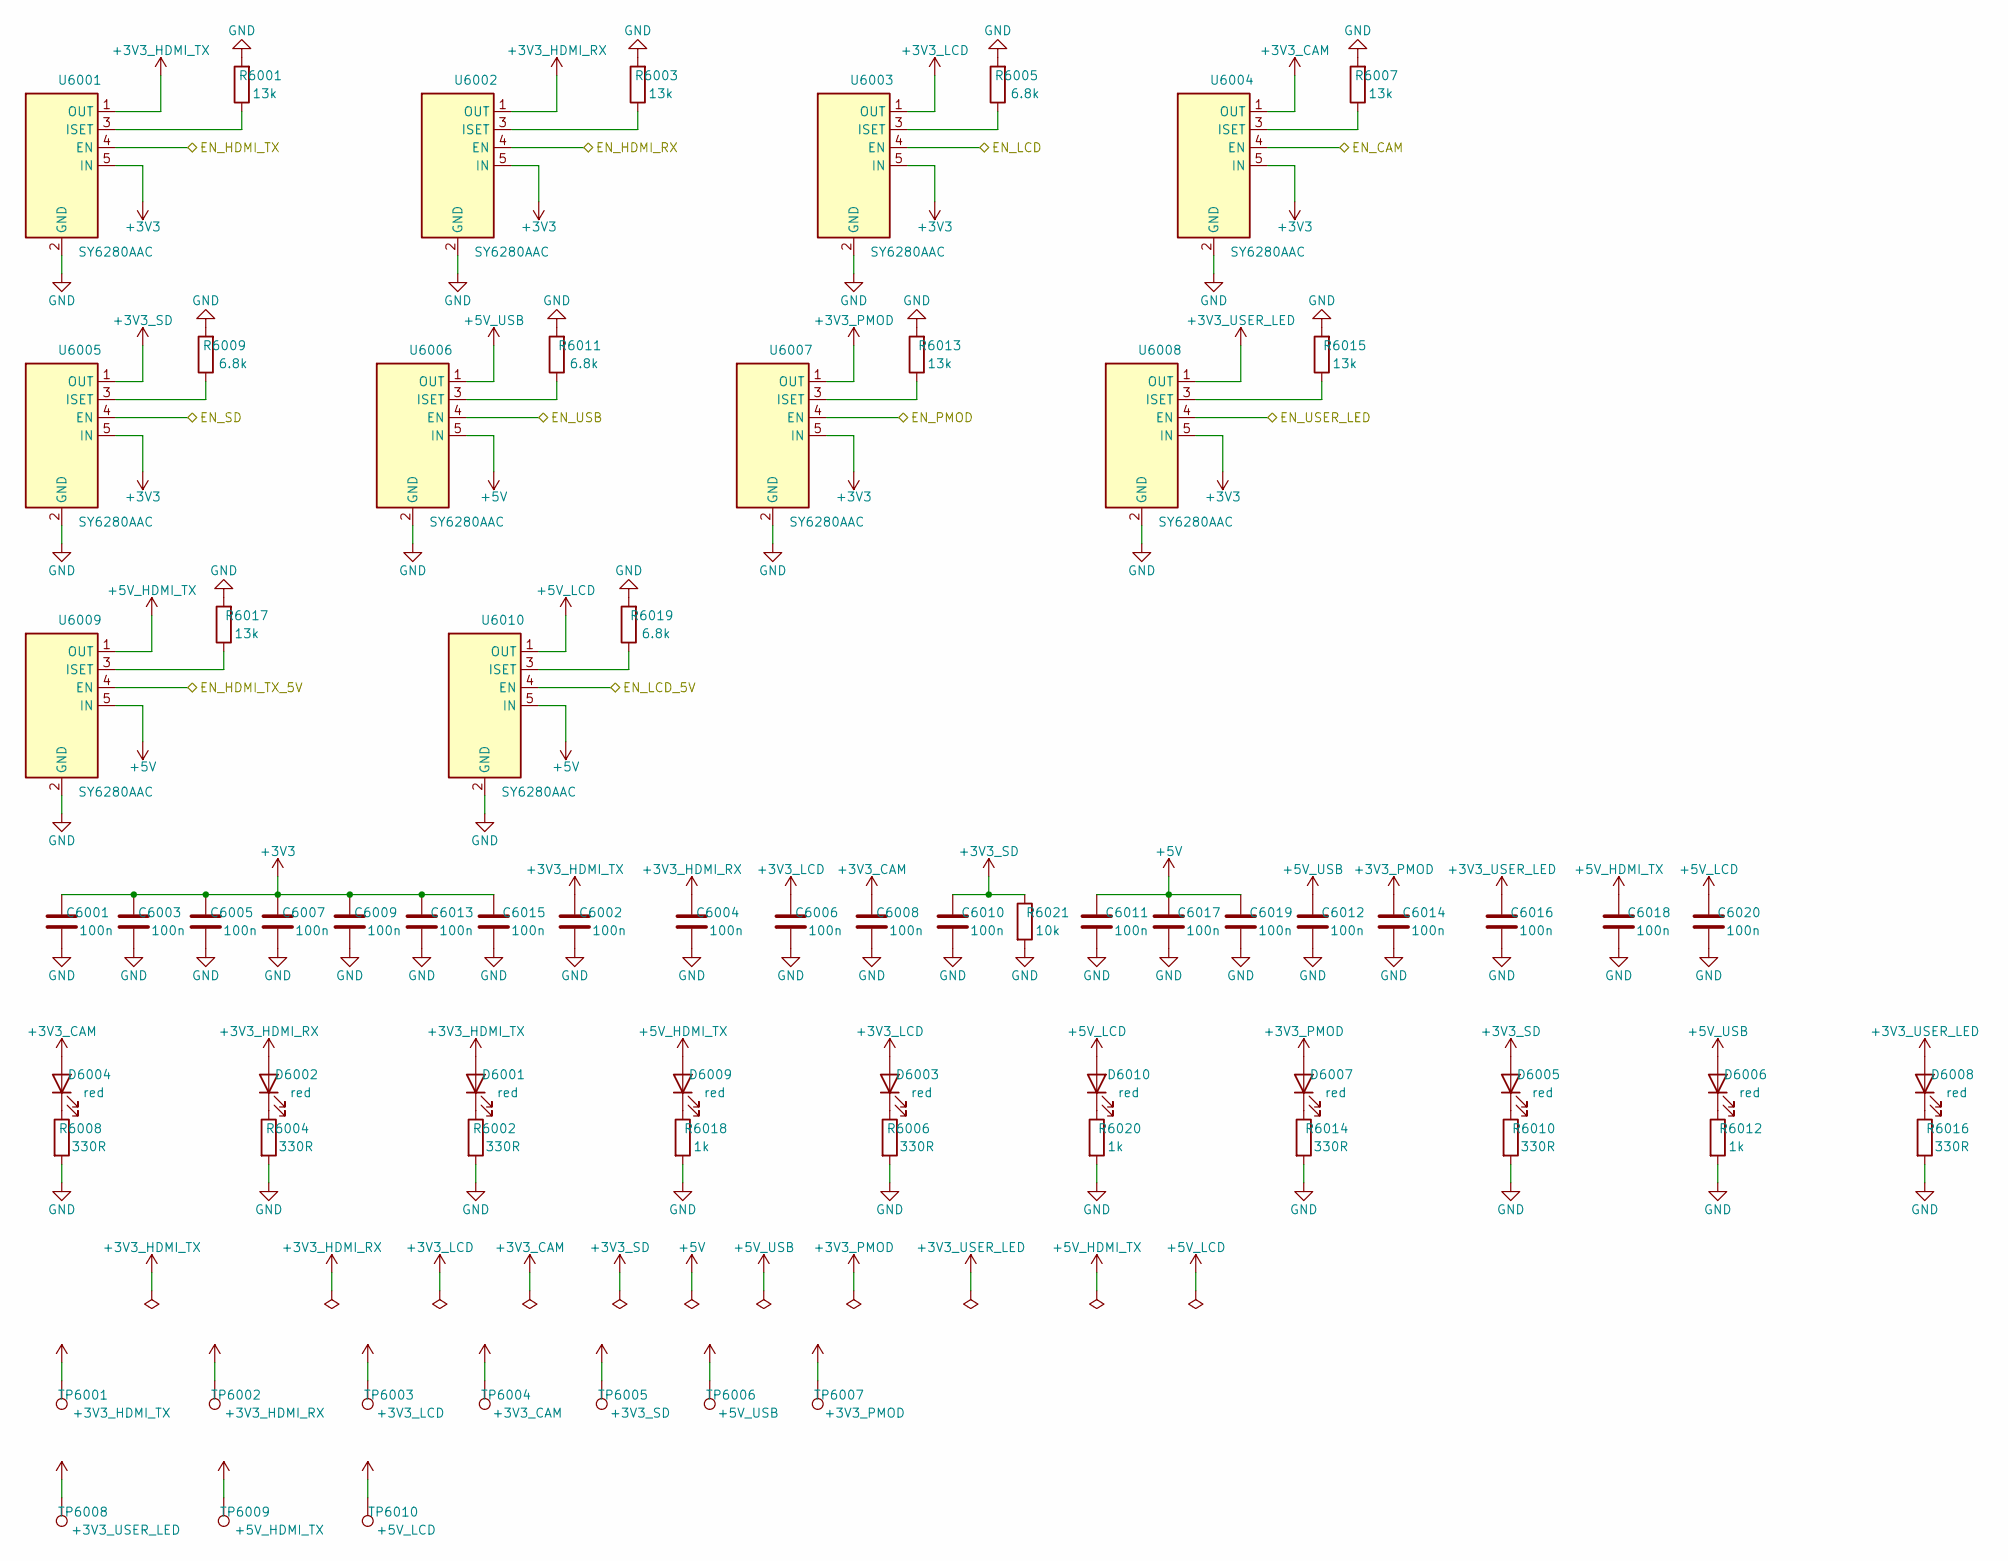
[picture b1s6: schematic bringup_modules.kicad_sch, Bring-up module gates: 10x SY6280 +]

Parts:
C6001, C6002, C6003, C6004, C6005, C6006, C6007, C6008, C6009, C6010, C6011, C6012, C6013, C6014, C6015, C6016, C6017, C6018, C6019, C6020: 100n; C_0603_1608Metric; LCSC C14663
D6001, D6002, D6003, D6004, D6005, D6006, D6007, D6008, D6009, D6010: red; LED_0603_1608Metric; LCSC C2286
R6001, R6003, R6007, R6013, R6015, R6017: 13k; R_0603_1608Metric; LCSC C22797
R6002, R6004, R6006, R6008, R6010, R6014, R6016: 330R; R_0603_1608Metric; LCSC C23138
R6005, R6009, R6011, R6019: 6.8k; R_0603_1608Metric; LCSC C23212
R6012, R6018, R6020: 1k; R_0603_1608Metric; LCSC C21190
R6021: 10k; R_0603_1608Metric; LCSC C25804
TP6001: +3V3_HDMI_TX; TestPoint_Pad_D1.5mm
TP6002: +3V3_HDMI_RX; TestPoint_Pad_D1.5mm
TP6003: +3V3_LCD; TestPoint_Pad_D1.5mm
TP6004: +3V3_CAM; TestPoint_Pad_D1.5mm
TP6005: +3V3_SD; TestPoint_Pad_D1.5mm
TP6006: +5V_USB; TestPoint_Pad_D1.5mm
TP6007: +3V3_PMOD; TestPoint_Pad_D1.5mm
TP6008: +3V3_USER_LED; TestPoint_Pad_D1.5mm
TP6009: +5V_HDMI_TX; TestPoint_Pad_D1.5mm
TP6010: +5V_LCD; TestPoint_Pad_D1.5mm
U6001, U6002, U6003, U6004, U6005, U6006, U6007, U6008, U6009, U6010: SY6280AAC; LCSC C55136

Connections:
+3V3: C6001.1, C6003.1, C6005.1, C6007.1, C6009.1, C6013.1, C6015.1, U6001.5 (IN), U6002.5 (IN), U6003.5 (IN), U6004.5 (IN), U6005.5 (IN), U6007.5 (IN), U6008.5 (IN); also elsewhere on the board
+3V3_CAM: C6008.1, D6004.2 (A), TP6004.1, U6004.1 (OUT); also elsewhere on the board
+3V3_HDMI_RX: C6004.1, D6002.2 (A), TP6002.1, U6002.1 (OUT); also elsewhere on the board
+3V3_HDMI_TX: C6002.1, D6001.2 (A), TP6001.1, U6001.1 (OUT); also elsewhere on the board
+3V3_LCD: C6006.1, D6003.2 (A), TP6003.1, U6003.1 (OUT); also elsewhere on the board
+3V3_PMOD: C6014.1, D6007.2 (A), TP6007.1, U6007.1 (OUT); also elsewhere on the board
+3V3_SD: C6010.1, D6005.2 (A), R6021.1, TP6005.1, U6005.1 (OUT); also elsewhere on the board
+3V3_USER_LED: C6016.1, D6008.2 (A), TP6008.1, U6008.1 (OUT); also elsewhere on the board
+5V: C6011.1, C6017.1, C6019.1, U6006.5 (IN), U6009.5 (IN), U6010.5 (IN); also elsewhere on the board
+5V_HDMI_TX: C6018.1, D6009.2 (A), TP6009.1, U6009.1 (OUT); also elsewhere on the board
+5V_LCD: C6020.1, D6010.2 (A), TP6010.1, U6010.1 (OUT); also elsewhere on the board
+5V_USB: C6012.1, D6006.2 (A), TP6006.1, U6006.1 (OUT); also elsewhere on the board
EN_CAM: U6004.4 (EN); also elsewhere on the board
EN_HDMI_RX: U6002.4 (EN); also elsewhere on the board
EN_HDMI_TX: U6001.4 (EN); also elsewhere on the board
EN_HDMI_TX_5V: U6009.4 (EN); also elsewhere on the board
EN_LCD: U6003.4 (EN); also elsewhere on the board
EN_LCD_5V: U6010.4 (EN); also elsewhere on the board
EN_PMOD: U6007.4 (EN); also elsewhere on the board
EN_SD: U6005.4 (EN); also elsewhere on the board
EN_USB: U6006.4 (EN); also elsewhere on the board
EN_USER_LED: U6008.4 (EN); also elsewhere on the board
GND: C6001.2, C6002.2, C6003.2, C6004.2, C6005.2, C6006.2, C6007.2, C6008.2, C6009.2, C6010.2, C6011.2, C6012.2, C6013.2, C6014.2, C6015.2, C6016.2, C6017.2, C6018.2, C6019.2, C6020.2, R6001.2, R6002.2, R6003.2, R6004.2, R6005.2, R6006.2, R6007.2, R6008.2, R6009.2, R6010.2, R6011.2, R6012.2, R6013.2, R6014.2, R6015.2, R6016.2, R6017.2, R6018.2, R6019.2, R6020.2, R6021.2, U6001.2 (GND), U6002.2 (GND), U6003.2 (GND), U6004.2 (GND), U6005.2 (GND), U6006.2 (GND), U6007.2 (GND), U6008.2 (GND), U6009.2 (GND), U6010.2 (GND); also elsewhere on the board
unnamed: D6001.1 (K), R6002.1
unnamed: D6002.1 (K), R6004.1
unnamed: D6003.1 (K), R6006.1
unnamed: D6004.1 (K), R6008.1
unnamed: D6005.1 (K), R6010.1
unnamed: D6006.1 (K), R6012.1
unnamed: D6007.1 (K), R6014.1
unnamed: D6008.1 (K), R6016.1
unnamed: D6009.1 (K), R6018.1
unnamed: D6010.1 (K), R6020.1
unnamed: R6001.1, U6001.3 (ISET)
unnamed: R6003.1, U6002.3 (ISET)
unnamed: R6005.1, U6003.3 (ISET)
unnamed: R6007.1, U6004.3 (ISET)
unnamed: R6009.1, U6005.3 (ISET)
unnamed: R6011.1, U6006.3 (ISET)
unnamed: R6013.1, U6007.3 (ISET)
unnamed: R6015.1, U6008.3 (ISET)
unnamed: R6017.1, U6009.3 (ISET)
unnamed: R6019.1, U6010.3 (ISET)
